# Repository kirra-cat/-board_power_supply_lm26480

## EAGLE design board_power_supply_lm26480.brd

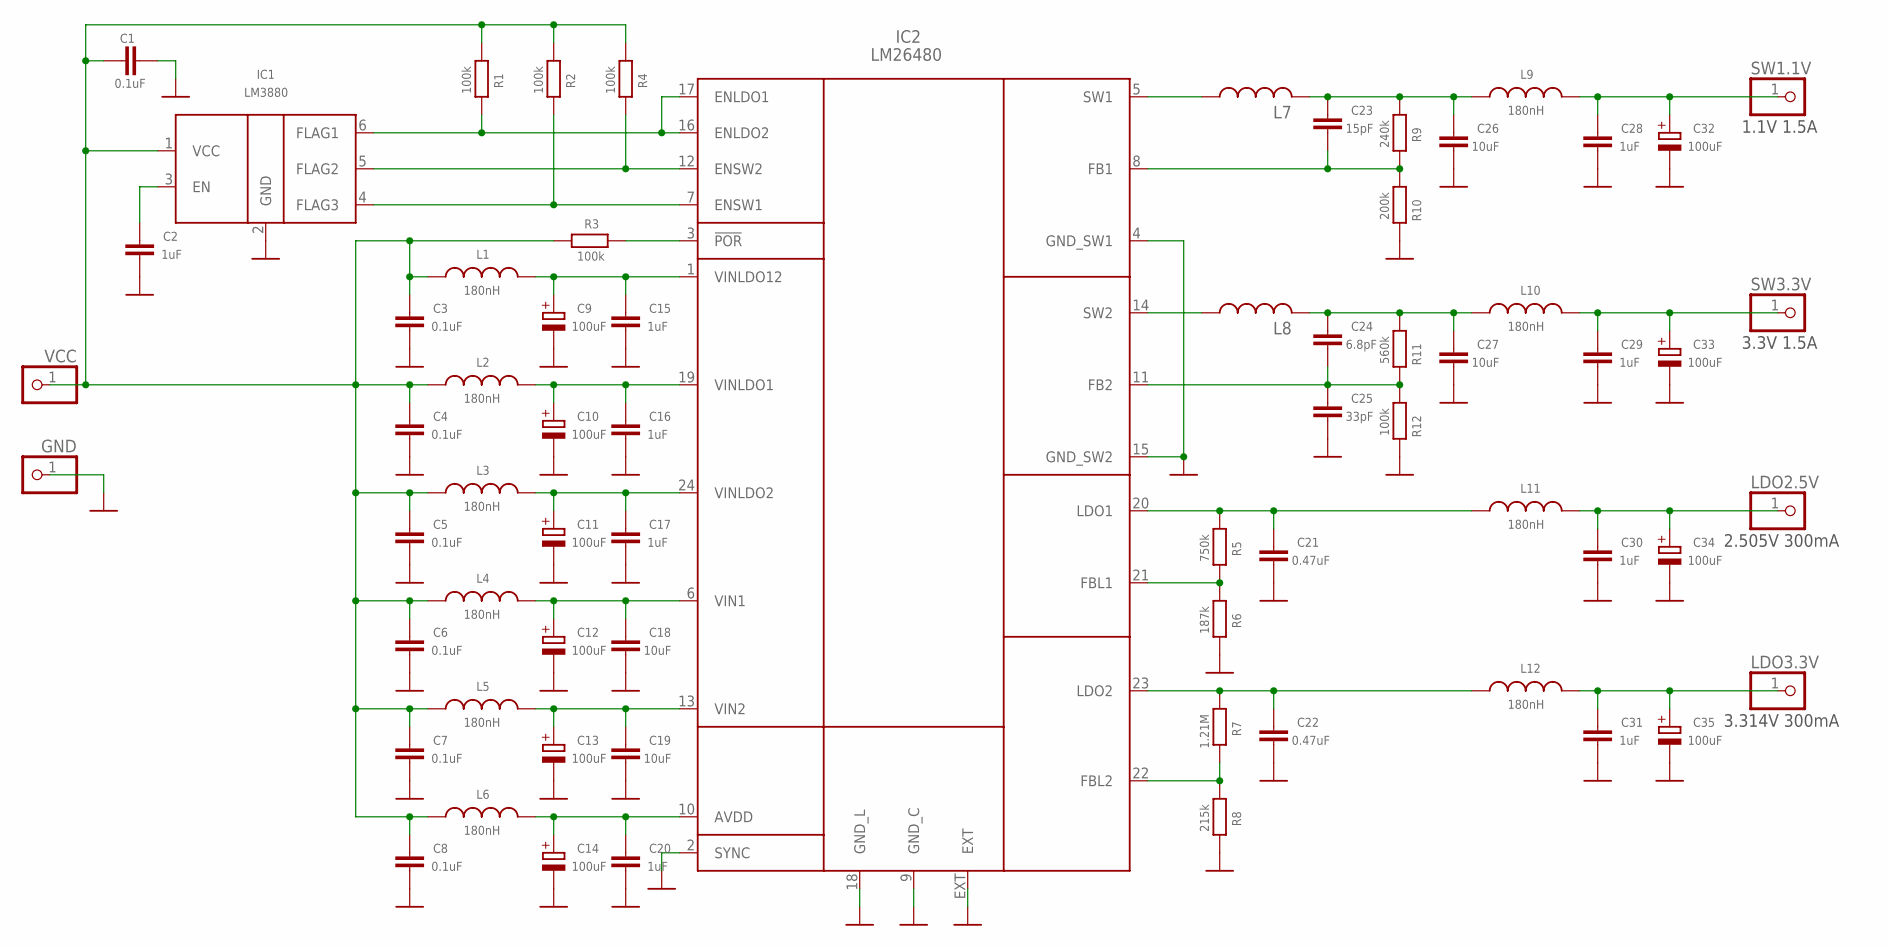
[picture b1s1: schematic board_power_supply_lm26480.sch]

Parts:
C1, C3, C4, C5, C6, C7, C8: 0.1uF; SMD0603
C2, C28, C29, C30, C31: 1uF; SMD0603
C9, C10, C11, C12, C13, C14, C32, C33, C34, C35: 100uF; SMC_B
C15, C16, C17, C20: 1uF; SMD0402
C18, C19, C26, C27: 10uF; SMD0805
C21, C22: 0.47uF; SMD0603
C23: 15pF; SMD0603
C24: 6.8pF; SMD0603
C25: 33pF; SMD0603
GND: PINHD-1X1; 1X01
IC1: LM3880; SOT23-6
IC2: LM26480; WQFN24
L1, L2, L3, L4, L5, L6, L9, L10, L11, L12: 180nH; SMD0603
L7, L8: L2825; L2825P
LDO2.5V, LDO3.3V: PINHD-1X1; 1X01
R1, R2, R4, R12: 100k; SMD0603
R3: 100k; SMD0402
R5: 750k; SMD0603
R6: 187k; SMD0603
R7: 1.21M; SMD0603
R8: 215k; SMD0603
R9: 240k; SMD0603
R10: 200k; SMD0603
R11: 560k; SMD0603
SW1.1V, SW3.3V: PINHD-1X1; 1X01
VCC: PINHD-1X1; 1X01

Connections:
GND: C1.1, C2.2, C3.2, C4.2, C5.2, C6.2, C7.2, C8.2, C9.-, C10.-, C11.-, C12.-, C13.-, C14.-, C15.2, C16.2, C17.2, C18.2, C19.2, C20.2, C21.2, C22.2, C25.2, C26.2, C27.2, C28.2, C29.2, C30.2, C31.2, C32.-, C33.-, C34.-, C35.-, GND.1, IC1.2 (GND), IC2.2 (SYNC), IC2.4 (GND_SW1), IC2.9 (GND_C), IC2.15 (GND_SW2), IC2.18 (GND_L), IC2.EXT, R6.1, R8.1, R10.1, R12.1
unnamed: C23.1, C26.1, L7.2, L9.1, R9.2
unnamed: C23.2, IC2.8 (FB1), R9.1, R10.2
unnamed: IC2.5 (SW1), L7.1
unnamed: C24.2, C25.1, IC2.11 (FB2), R11.1, R12.2
unnamed: IC2.14 (SW2), L8.1
unnamed: IC2.3 (!POR), R3.1
unnamed: C9.+, C15.1, IC2.1 (VINLDO12), L1.2
unnamed: IC2.21 (FBL1), R5.1, R6.2
unnamed: IC2.22 (FBL2), R7.1, R8.2
unnamed: C21.1, IC2.20 (LDO1), L11.1, R5.2
unnamed: C10.+, C16.1, IC2.19 (VINLDO1), L2.2
unnamed: C11.+, C17.1, IC2.24 (VINLDO2), L3.2
unnamed: C12.+, C18.1, IC2.6 (VIN1), L4.2
unnamed: C24.1, C27.1, L8.2, L10.1, R11.2
unnamed: C13.+, C19.1, IC2.13 (VIN2), L5.2
unnamed: C14.+, C20.1, IC2.10 (AVDD), L6.2
unnamed: C28.1, C32.+, L9.2, SW1.1V.1
unnamed: C29.1, C33.+, L10.2, SW3.3V.1
unnamed: C30.1, C34.+, L11.2, LDO2.5V.1
unnamed: C22.1, IC2.23 (LDO2), L12.1, R7.2
unnamed: C31.1, C35.+, L12.2, LDO3.3V.1
unnamed: IC1.5 (FLAG2), IC2.12 (ENSW2), R4.1
unnamed: IC1.4 (FLAG3), IC2.7 (ENSW1), R2.1
unnamed: IC1.6 (FLAG1), IC2.16 (ENLDO2), IC2.17 (ENLDO1), R1.1
unnamed: C2.1, IC1.3 (EN)
VCC: C1.2, C3.1, C4.1, C5.1, C6.1, C7.1, C8.1, IC1.1 (VCC), L1.1, L2.1, L3.1, L4.1, L5.1, L6.1, R1.2, R2.2, R3.2, R4.2, VCC.1

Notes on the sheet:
1.1V 1.5A
3.3V 1.5A
2.505V 300mA
3.314V 300mA

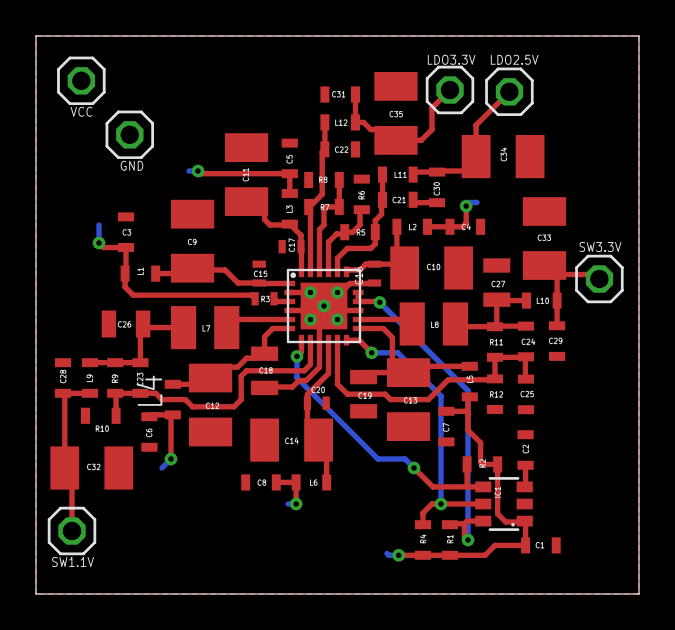
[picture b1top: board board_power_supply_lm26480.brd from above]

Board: 2 copper layers, 33.5 x 31.0 mm, 67 parts (0 on the bottom side), 27 nets.

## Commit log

2016-07-31 Первая версия схемы и трассировки
